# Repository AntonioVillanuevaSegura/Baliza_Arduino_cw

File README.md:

# Baliza_Arduino_cw
Modificacion del programa de EA7HG  por F4LEC , para simulacion ,

Posibilidad de cambiar WPM 
Cambio de mensaje linea 13 String mensaje = "";  //Mensaje a enviar por la baliza
Debug RS232

( entre comentarios esta el codigo para modo real , no simulacion ,  no probado )

Link a simulacion con el codigo C++ modificado 
https://wokwi.com/projects/454496346094658561

La tarjeta PCB tiene un diodo de proteccion de polaridad a la entrada
He previsto la PCB con 3 salidas adicionales con LED ,pero la base sigue siendo la misma 

La CPU es una Arduino nano , resistencia de 1/4 de W ....

Hay una carpeta GERBER con un fichero comprimido baliza.zip que es 
compatible con el formato de https://jlcpcb.com por ejemplo 

El tipo de rele que voy a utilizar 
PC, JQC-3F(T73), DC5V Bobine, SPDT, 7A 240VAC Bornes 5 broches
https://www.amazon.fr/dp/B074599SN8?ref=ppx_yo2ov_dt_b_fed_asin_title

Los conectores
5mm PCB Vis Connecteur, Bornier à Souder Vert, 2
https://www.amazon.fr/dp/B0DSBSXL47?ref=ppx_yo2ov_dt_b_fed_asin_title

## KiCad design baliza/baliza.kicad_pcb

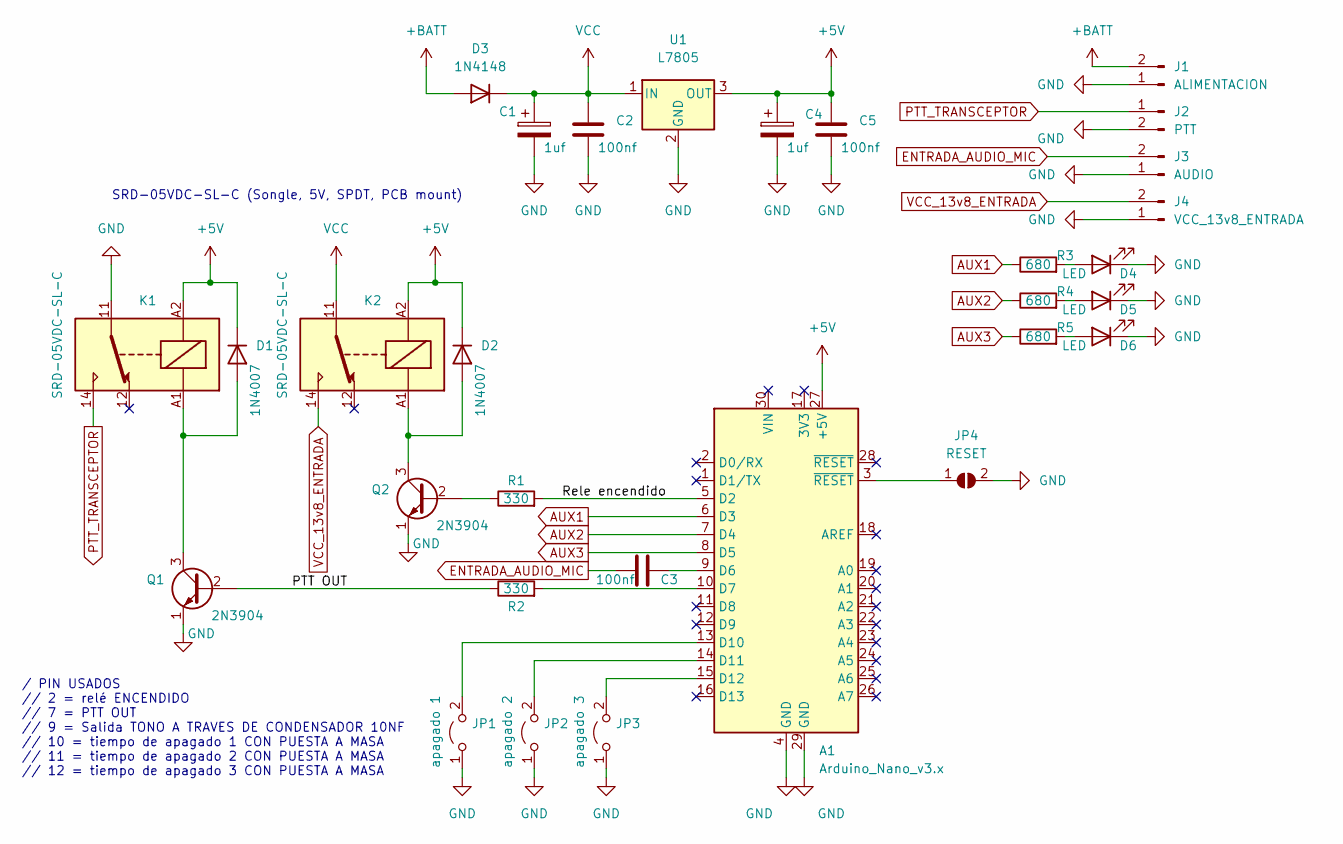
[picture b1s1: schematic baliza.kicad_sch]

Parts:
A1: Arduino_Nano_v3.x; Arduino_Nano
C1, C4: 1uf; CP_Radial_D5.0mm_P2.00mm
C2, C3, C5: 100nf; C_Disc_D4.7mm_W2.5mm_P5.00mm
D1, D2: 1N4007; D_DO-41_SOD81_P10.16mm_Horizontal
D3: 1N4148; D_DO-35_SOD27_P7.62mm_Horizontal
D4, D5, D6: LED; LED_D5.0mm
J1: ALIMENTACION; TerminalBlock_RND_205-00001_1x02_P5.00mm_Horizontal
J2: PTT; TerminalBlock_RND_205-00001_1x02_P5.00mm_Horizontal
J3: AUDIO; TerminalBlock_RND_205-00001_1x02_P5.00mm_Horizontal
J4: VCC_13v8_ENTRADA; TerminalBlock_RND_205-00001_1x02_P5.00mm_Horizontal
JP1: apagado 1; PinHeader_1x02_P2.54mm_Vertical
JP2: apagado 2; PinHeader_1x02_P2.54mm_Vertical
JP3: apagado 3; PinHeader_1x02_P2.54mm_Vertical
JP4: RESET; PinHeader_1x02_P2.54mm_Vertical
K1, K2: SRD-05VDC-SL-C; Relay_SPDT_Finder_36.11
Q1, Q2: 2N3904; TO-92_Inline
R1, R2: 330; R_Axial_DIN0204_L3.6mm_D1.6mm_P5.08mm_Horizontal
R3, R4, R5: 680; R_Axial_DIN0204_L3.6mm_D1.6mm_P5.08mm_Horizontal
U1: L7805; TO-220-3_Vertical

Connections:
+5V: A1.27 (+5V), C4.1, C5.1, D1.1 (K), D2.1 (K), K1.A2, K2.A2, U1.3 (OUT)
+BATT: D3.2 (A), J1.2
/PTT OUT: Q1.2 (B), R2.1
/Rele encendido: A1.5 (D2), R1.2
AUX1: A1.6 (D3), R3.1
AUX2: A1.7 (D4), R4.1
AUX3: A1.8 (D5), R5.1
ENTRADA_AUDIO_MIC: C3.1, J3.2
GND: A1.4 (GND), A1.29 (GND), C1.2, C2.2, C4.2, C5.2, D4.1 (K), D5.1 (K), D6.1 (K), J1.1, J2.2, J3.1, J4.1, JP1.1 (A), JP2.1 (A), JP3.1 (A), JP4.2 (B), K1.11, Q1.1 (E), Q2.1 (E), U1.2 (GND)
unnamed: A1.3 (~RESET), JP4.1 (A)
unnamed: A1.9 (D6), C3.2
unnamed: A1.10 (D7), R2.2
unnamed: A1.13 (D10), JP1.2 (B)
unnamed: A1.14 (D11), JP2.2 (B)
unnamed: A1.15 (D12), JP3.2 (B)
unnamed: D1.2 (A), K1.A1, Q1.3 (C)
unnamed: D2.2 (A), K2.A1, Q2.3 (C)
unnamed: D4.2 (A), R3.2
unnamed: D5.2 (A), R4.2
unnamed: D6.2 (A), R5.2
unnamed: Q2.2 (B), R1.1
PTT_TRANSCEPTOR: J2.1, K1.14
VCC: C1.1, C2.1, D3.1 (K), K2.11, U1.1 (IN)
VCC_13v8_ENTRADA: J4.2, K2.14

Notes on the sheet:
/ PIN USADOS // 2 = relé ENCENDIDO // 7 = PTT OUT // 9 = Salida TONO A TRAVES DE CONDENSADOR 10NF // 10 = tiempo de apagado 1 CON PUESTA A MASA // 11 = tiempo de apagado 2 CON PUESTA A MASA // 12 = tiempo de apagado 3 CON PUESTA A MASA
SRD-05VDC-SL-C (Songle, 5V, SPDT, PCB mount)

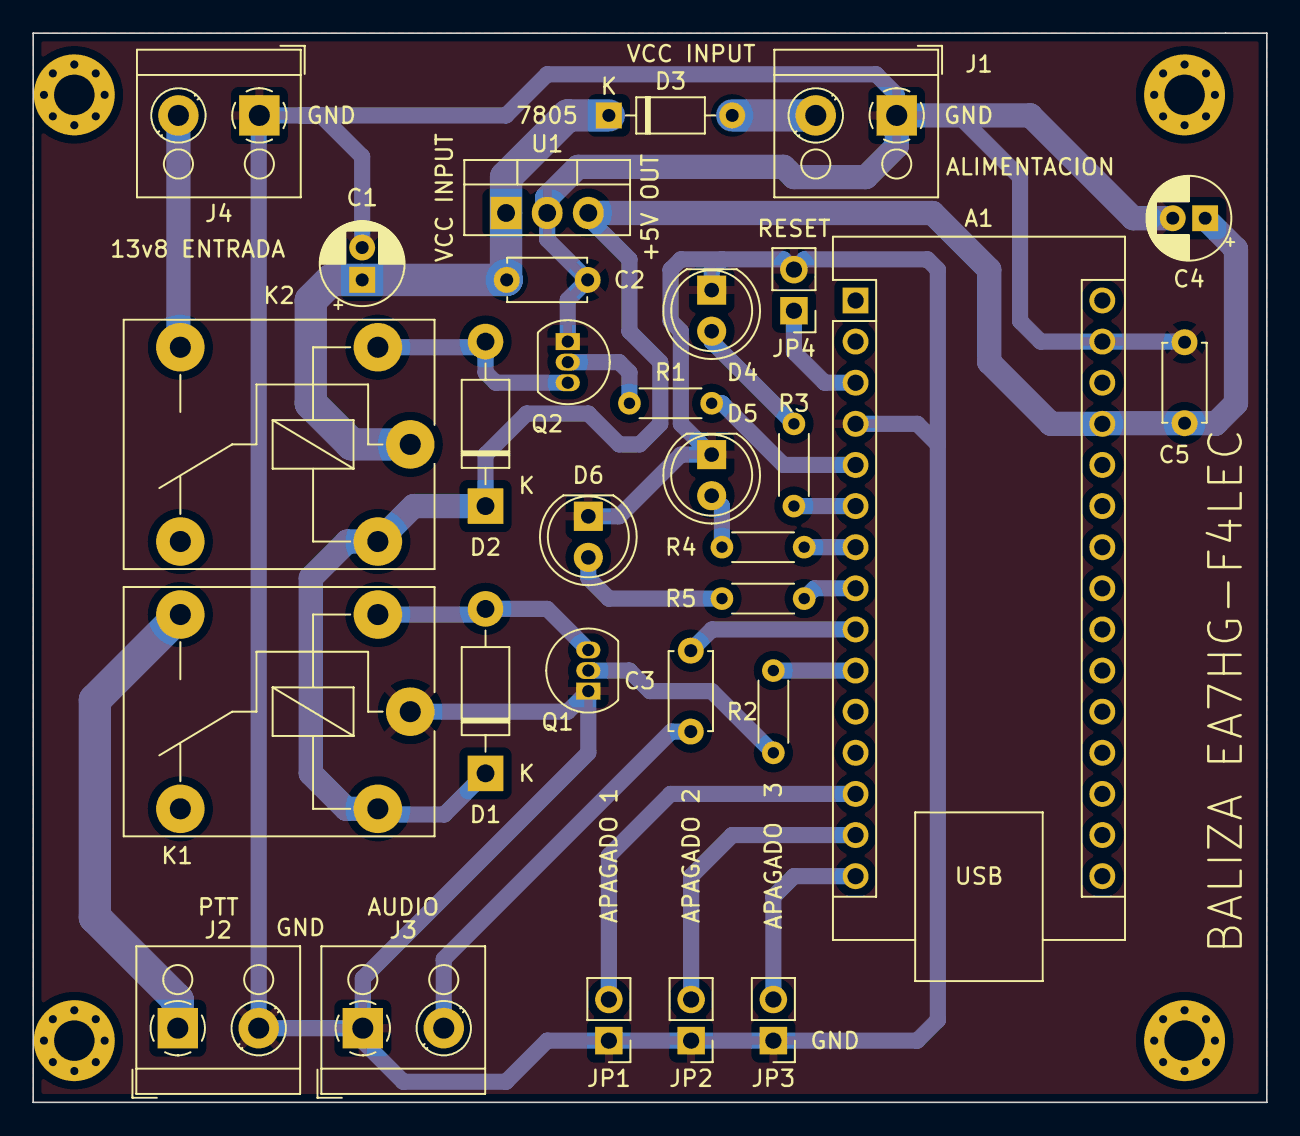
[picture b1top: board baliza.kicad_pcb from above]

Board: 2 copper layers, 76.2 x 66.0 mm, 30 parts (0 on the bottom side), 24 nets.

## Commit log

2026-01-30 kicad
2026-01-30 esquemas pdf de kicad
2026-01-30 comentarios
2026-01-30 imagen
2026-01-30 esquema
2026-01-30 actualizacion
2026-01-31 anadir LEDs auxiliares, pistas en cara inferior
2026-01-31 gerber
2026-01-31 fotos gerbers
2026-02-11 image
2026-02-11 version pcb
2026-02-11 version 2
2026-02-11 borra
2026-02-11 version 2 simulacion PCB
2026-02-11 linea
2026-02-14 SALIDA 6 es D6 pin fisico 9 de arduino NANO salida audio
2026-02-14 README fotos
2026-02-14 README
